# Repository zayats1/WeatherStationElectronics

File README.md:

An electronics for my weather station

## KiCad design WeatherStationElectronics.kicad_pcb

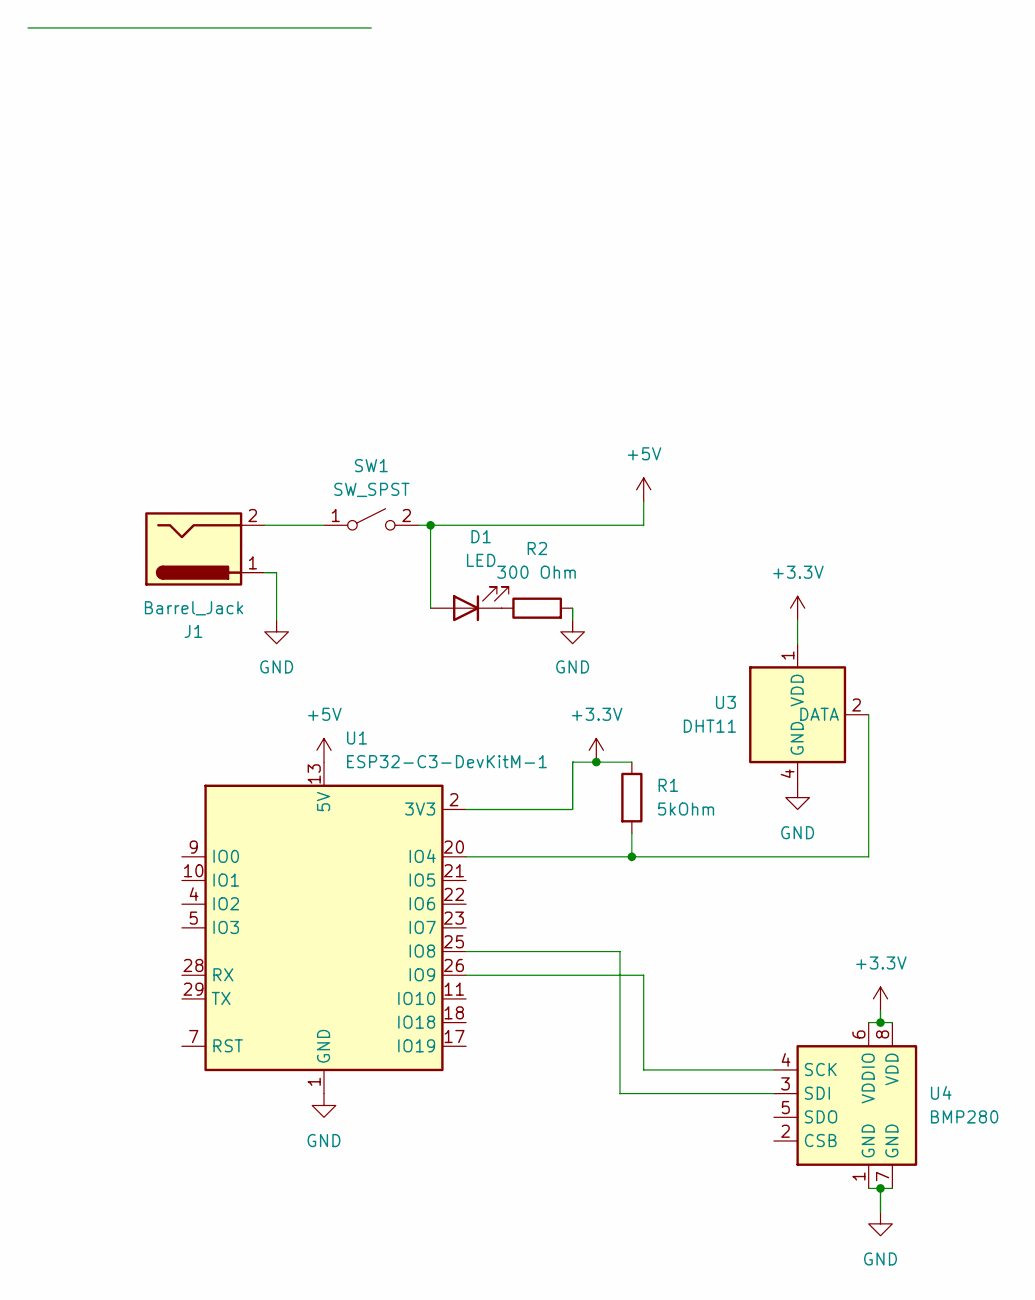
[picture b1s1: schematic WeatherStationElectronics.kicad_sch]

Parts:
D1: LED; LED_D5.0mm_Clear
J1: Barrel_Jack; BarrelJack_CUI_PJ-063AH_Horizontal
R1: 5kOhm; R_Axial_DIN0411_L9.9mm_D3.6mm_P12.70mm_Horizontal
R2: 300 Ohm; R_Axial_DIN0516_L15.5mm_D5.0mm_P20.32mm_Horizontal
SW1: SW_SPST; SW_MEC_5GSH9
U1: ESP32-C3-DevKitM-1
U3: DHT11; Aosong_DHT11_5.5x12.0_P2.54mm
U4: BMP280; Bosch_LGA-8_2x2.5mm_P0.65mm_ClockwisePinNumbering

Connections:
+3.3V: R1.1, U1.2 (3V3), U1.3 (3V3), U3.1 (VDD), U4.6 (VDDIO), U4.8 (VDD)
+5V: D1.2 (A), SW1.2 (B), U1.13 (5V), U1.14 (5V)
GND: J1.1, R2.2, U1.1 (GND), U1.6 (GND), U1.8 (GND), U1.12 (GND), U1.15 (GND), U1.16 (GND), U1.19 (GND), U1.24 (GND), U1.27 (GND), U1.30 (GND), U3.4 (GND), U4.1 (GND), U4.7 (GND)
unnamed: D1.1 (K), R2.1
unnamed: J1.2, SW1.1 (A)
unnamed: R1.2, U1.20 (IO4), U3.2 (DATA)
unnamed: U1.25 (IO8), U4.3 (SDI)
unnamed: U1.26 (IO9), U4.4 (SCK)

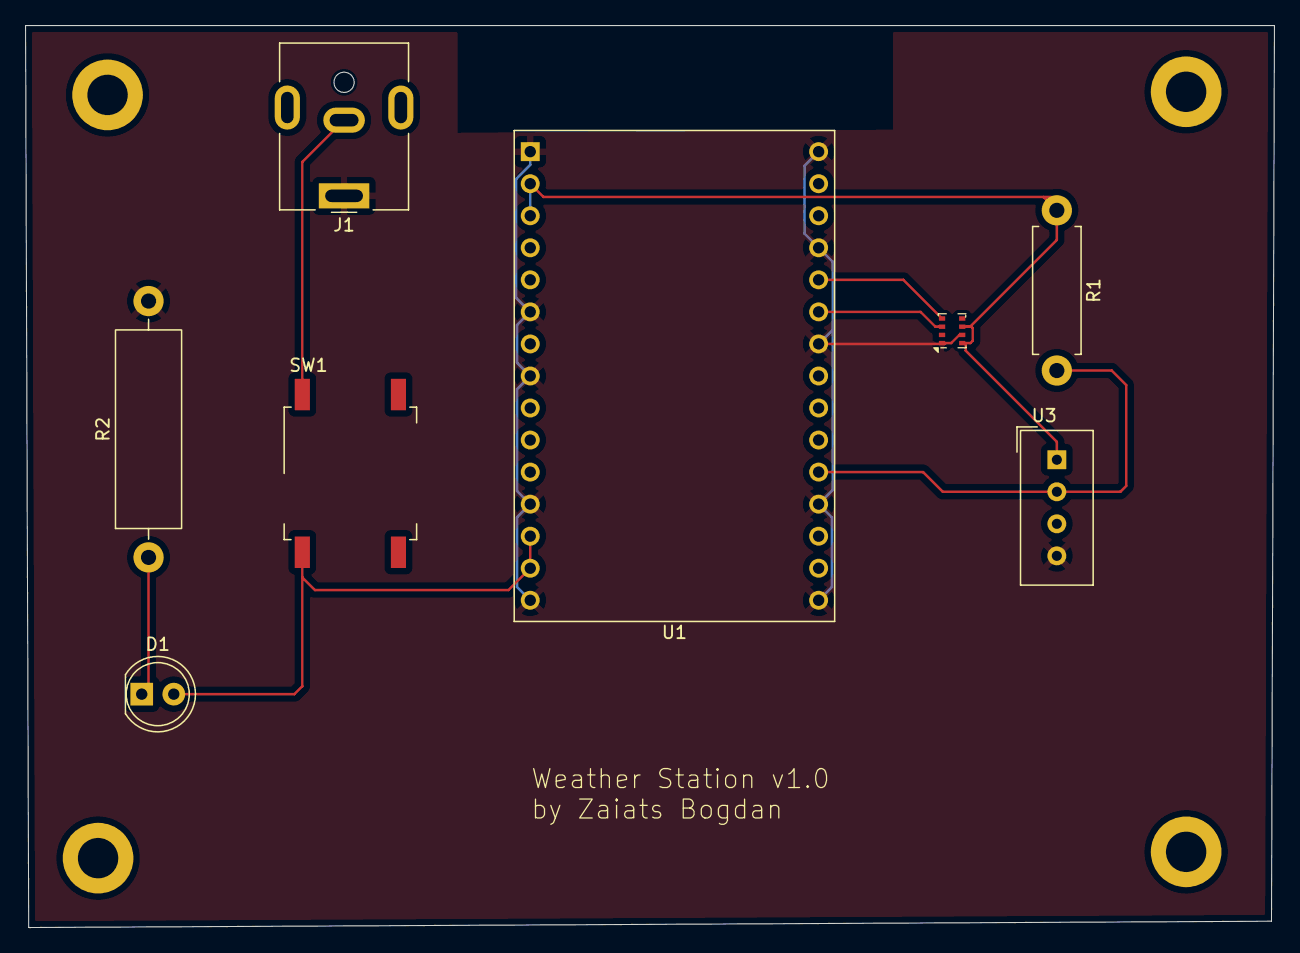
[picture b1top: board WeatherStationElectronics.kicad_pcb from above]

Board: 2 copper layers, 99.0 x 71.5 mm, 9 parts (0 on the bottom side), 8 nets.

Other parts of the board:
M3: MountingHole_3.2mm_M3_DIN965_Pad

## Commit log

2025-06-17 Create LICENSE
2025-06-24 first PCB
    todo: add a power switch
2025-06-25 update PCB and add a power switch
2025-07-08 define a pcb outline
2025-07-08 backup
2025-07-19 Add mounting holes to the PCB
2025-07-19 update PCB
    Make mounting holes and fill all the board area with copper connected to
    the ground
2025-07-29 Added a keepout area under the antena
2025-07-29 ignore backups
2025-07-29 added a keepout zone under the antena
2025-07-29 ignore backups in GIT
